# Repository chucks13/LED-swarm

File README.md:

# LED-swarm
Arduino based radio synced addressable LEDstrips

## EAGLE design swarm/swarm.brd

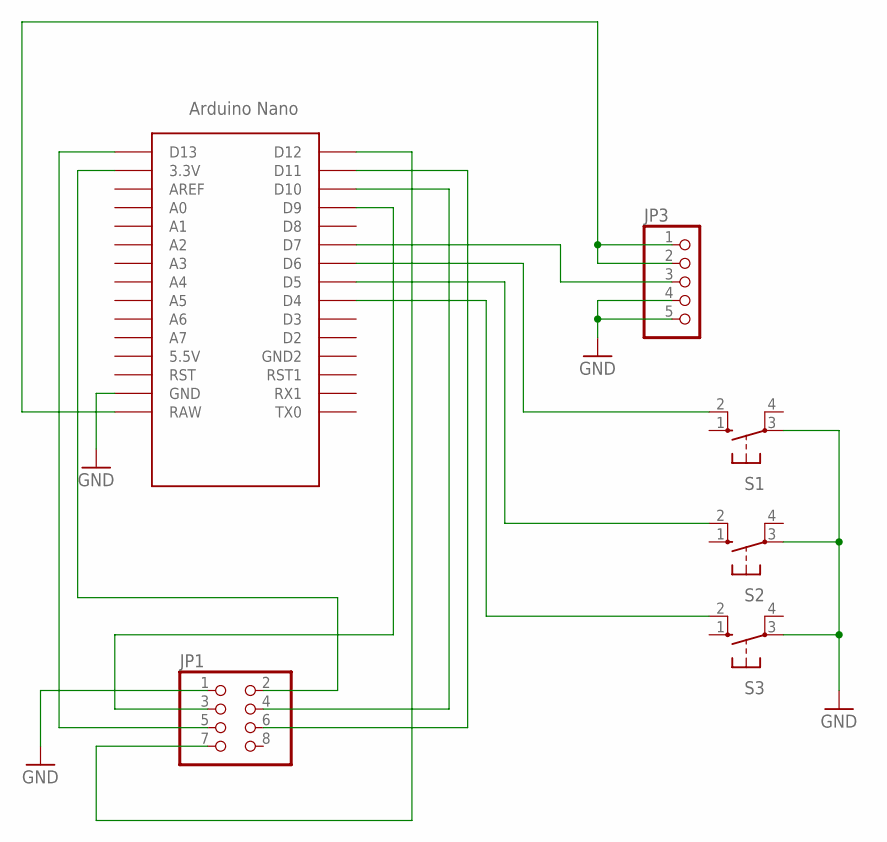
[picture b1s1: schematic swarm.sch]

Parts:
JP1: PINHD-2X4; 2X04
JP3: PINHD-1X5; 1X05
S1, S2, S3: 10-XX; B3F-10XX
U$1: NANO

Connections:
GND: JP1.1, JP3.4, JP3.5, S1.3, S2.3, S3.3, U$1.GND
unnamed: JP3.3, U$1.D7
unnamed: JP3.1, JP3.2, U$1.RAW
unnamed: S1.2 (S1), U$1.D6
unnamed: JP1.7, U$1.D12
unnamed: JP1.5, U$1.D13
unnamed: JP1.3, U$1.D9
unnamed: JP1.6, U$1.D11
unnamed: JP1.4, U$1.D10
unnamed: JP1.2, U$1.3.3V
unnamed: S2.2 (S1), U$1.D5
unnamed: S3.2 (S1), U$1.D4

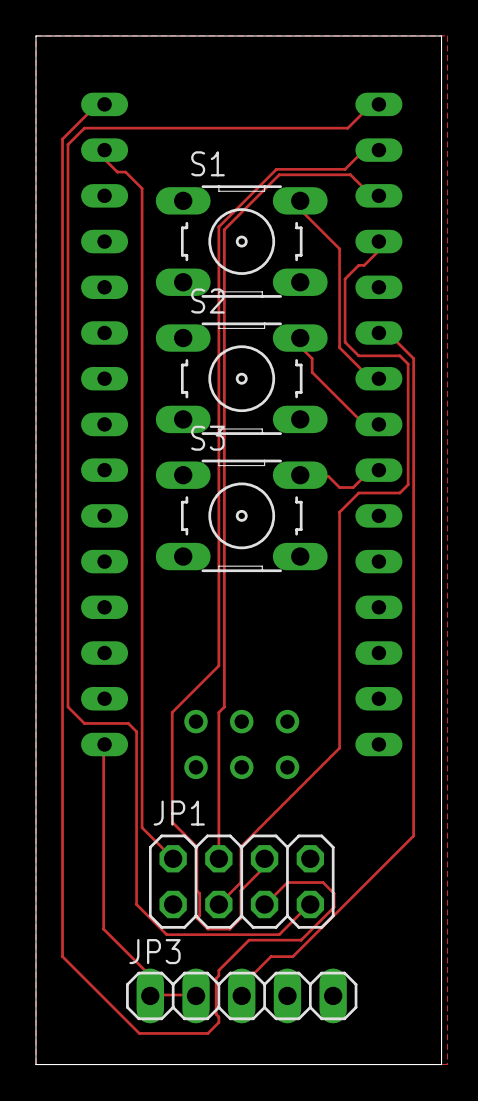
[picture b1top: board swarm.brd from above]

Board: 2 copper layers, 22.5 x 57.1 mm, 6 parts (0 on the bottom side), 12 nets.

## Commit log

2018-09-19 Add files via upload
    Initial check in
2018-09-19 Add files via upload
    added brightness control
2018-09-20 Add files via upload
    new sparkle effect
2018-09-20 Add files via upload
    minor change to theory describing NUM_LEDS
2018-09-20 Add files via upload
    started a parts list
2018-11-18 Add files via upload
    added perlin noise effect
2018-11-18 Add files via upload
    expanded the noise effect to 2 styles
2018-11-18 Add files via upload
    auto scaled some effects to display size
2018-11-30 Add files via upload
    board design
2018-12-13 Add files via upload
    added accelerator connector
2019-05-05 Added STL files
    Added STL files
2019-05-24 Add files via upload
    Release 5-23-2019
2019-05-25 timing update
    changed master/slave to leader/follower, changed millis() to micro(), Changed effect timeout to count up instead of down
2019-05-25 Delete led_swarm.ino
    out of date
2019-06-14 Strongman update
    adds function for strongman display for Illuminaughty carnival.
2019-06-15 Fixed some master timing
    fixed timeouts, and added a define for the strongman effect number which has changed from 10 to 200
2019-06-16 First draft of rev 2 swarm board wand assembly
    Probably has spelling errors.
2019-06-18 Assembly instructions in 3 parts
    splitting the instructions into 3 pdf files seems to make all the pictures show up
2019-06-18 split the instructions into 3 files
    bye bye single document
2019-06-19 swarm 3 board for teensy
    This board has an error on it. The analog pins were used for the radio instead of the digital pins.
2019-08-11 update
    updated mostly strongman code
